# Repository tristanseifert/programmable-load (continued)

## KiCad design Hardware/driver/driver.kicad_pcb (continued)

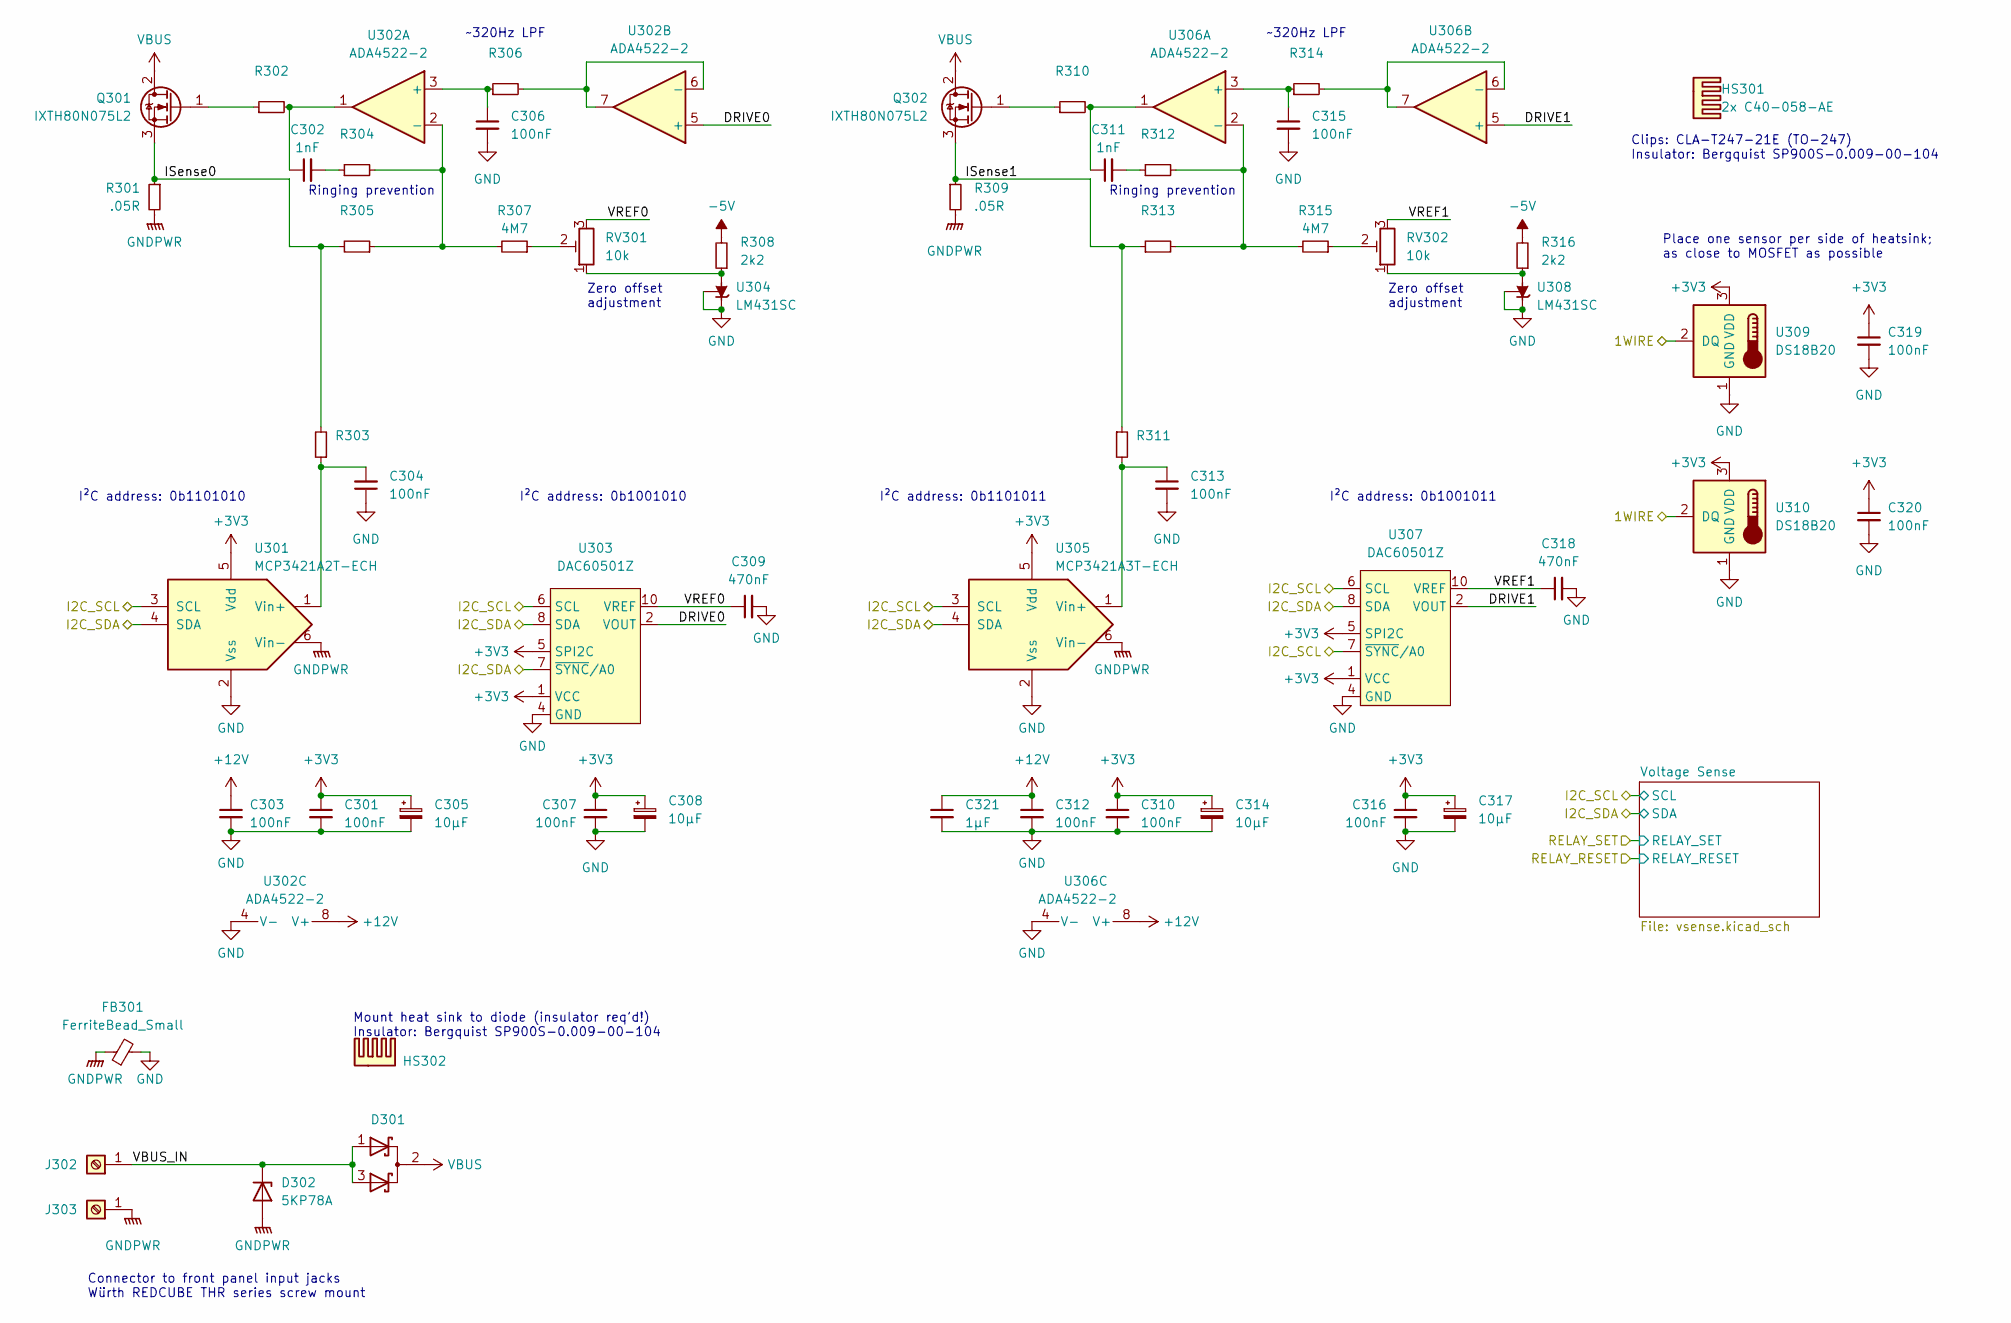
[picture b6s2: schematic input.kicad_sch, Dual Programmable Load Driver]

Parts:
C301, C303, C304, C306, C307, C310, C312, C313, C315, C316, C319, C320: 100nF; C_0805_2012Metric_Pad1.18x1.45mm_HandSolder
C302, C311: 1nF; C_0805_2012Metric_Pad1.18x1.45mm_HandSolder
C305, C308, C314, C317: 10µF; CP_EIA-3216-18_Kemet-A_Pad1.58x1.35mm_HandSolder; MPN TAJA106K016RNJ
C309, C318: 470nF; C_0805_2012Metric_Pad1.18x1.45mm_HandSolder; MPN CL21B474KAFNNNE
C321: 1µF; C_0805_2012Metric_Pad1.18x1.45mm_HandSolder; MPN CL21B105KBFNNNG
D301: DSA120C150QB; TO-247-3_Vertical; MPN DSA120C150QB
D302: 5KP78A; D_P600_R-6_P20.00mm_Horizontal; MPN 5KP78A
FB301: FerriteBead_Small; L_0805_2012Metric_Pad1.05x1.20mm_HandSolder; MPN MFBM1V2012-800-R
HS301: 2x C40-058-AE; C40-058-AE-DUAL; MPN C40-058-AE
HS302: WV-T247-101E; Ohmite-WA-T247-101E-MFG; MPN WV-T247-101E
J302, J303: Würth 74651194R; WE-74651194; MPN 74651194R
Q301, Q302: IXTH80N075L2; TO-247-3_Vertical
R301, R309: .05R; TO-247-2_Vertical
R302, R310: MPN WR08X101-JTL
R303, R306, R311, R314: MPN CR0805-FX-4991ELF
R304, R305, R312, R313: MPN CR0805-JW-102ELF
R307, R315: 4M7; R_0805_2012Metric_Pad1.20x1.40mm_HandSolder; MPN 260-4.7M-RC
R308, R316: 2k2; R_0805_2012Metric_Pad1.20x1.40mm_HandSolder; MPN RMC1/10-222JTP
RV301, RV302: 10k; Potentiometer_Nidec_Copal_CT94EY; MPN CT-94EY103
U301: MCP3421A2T-ECH; SOT-23-6_Handsoldering
U302, U306: ADA4522-2; SOIC-8_3.9x4.9mm_P1.27mm; MPN ADA4522-2ARZ
U303, U307: DAC60501Z; VSSOP-10_3x3mm_P0.5mm; MPN DAC60501ZDGSR
U304, U308: LM431SC; SOT-23; MPN LM431SCCMFX
U305: MCP3421A3T-ECH; SOT-23-6_Handsoldering
U309, U310: DS18B20; TO-92_Inline

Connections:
+3V3: C301.1, C305.1, C307.1, C308.1, C310.1, C314.1, C316.1, C317.1, C319.1, C320.1, U301.5 (Vdd), U303.1 (VCC), U303.5 (SPI2C), U305.5 (Vdd), U307.1 (VCC), U307.5 (SPI2C), U309.3 (VDD), U310.3 (VDD); also elsewhere on the board
+12V: C303.1, C312.1, C321.1, U302.8 (V+), U306.8 (V+); also elsewhere on the board
-5V: R308.2, R316.2; also elsewhere on the board
/1WIRE: U309.2 (DQ), U310.2 (DQ); also elsewhere on the board
/I2C_SCL: U301.3 (SCL), U303.6 (SCL), U305.3 (SCL), U307.6 (SCL), U307.7 (~SYNC/A0); also elsewhere on the board
/I2C_SDA: U301.4 (SDA), U303.7 (~SYNC/A0), U303.8 (SDA), U305.4 (SDA), U307.8 (SDA); also elsewhere on the board
/Input Stage/DRIVE0: U302.5 (+), U303.2 (VOUT)
/Input Stage/DRIVE1: U306.5 (+), U307.2 (VOUT)
/Input Stage/ISense0: Q301.3 (S), R301.1, R303.2, R305.2
/Input Stage/ISense1: Q302.3 (S), R309.1, R311.1, R313.1
/Input Stage/VBUS_IN: D301.1 (K), D301.3 (K), D302.1 (A1), J302.1
/Input Stage/VREF0: C309.1, RV301.3, U303.10 (VREF)
/Input Stage/VREF1: C318.1, RV302.3, U307.10 (VREF)
GND: C301.2, C303.2, C304.1, C305.2, C306.2, C307.2, C308.2, C309.2, C310.2, C312.2, C313.2, C314.2, C315.2, C316.2, C317.2, C318.2, C319.2, C320.2, C321.2, FB301.2, U301.2 (Vss), U302.4 (V-), U303.4 (GND), U304.1 (K), U304.2 (REF), U305.2 (Vss), U306.4 (V-), U307.4 (GND), U308.1 (K), U308.2 (REF), U309.1 (GND), U310.1 (GND); also elsewhere on the board
GNDPWR: D302.2 (A2), FB301.1, J303.1, R301.2, R309.2, U301.6 (Vin-), U305.6 (Vin-); also elsewhere on the board
unnamed: C302.1, R302.2, U302.1
unnamed: C302.2, R304.1
unnamed: C304.2, R303.1, U301.1 (Vin+)
unnamed: C306.1, R306.1, U302.3 (+)
unnamed: C311.1, R310.2, U306.1
unnamed: C311.2, R312.1
unnamed: C313.1, R311.2, U305.1 (Vin+)
unnamed: C315.1, R314.1, U306.3 (+)
unnamed: Q301.1 (G), R302.1
unnamed: Q302.1 (G), R310.1
unnamed: R304.2, R305.1, R307.2, U302.2 (-)
unnamed: R306.2, U302.6 (-), U302.7
unnamed: R307.1, RV301.2
unnamed: R308.1, RV301.1, U304.3 (A)
unnamed: R312.2, R313.2, R315.2, U306.2 (-)
unnamed: R314.2, U306.6 (-), U306.7
unnamed: R315.1, RV302.2
unnamed: R316.1, RV302.1, U308.3 (A)
VBUS: D301.2 (A), Q301.2 (D), Q302.2 (D); also elsewhere on the board

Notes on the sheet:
Zero offset adjustment
I²C address: 0b1101010
I²C address: 0b1001011
I²C address: 0b1001010
Clips: CLA-T247-21E (TO-247) Insulator: Bergquist SP900S-0.009-00-104
Ringing prevention
Place one sensor per side of heatsink; as close to MOSFET as possible
Connector to front panel input jacks Würth REDCUBE THR series screw mount
~320Hz LPF
I²C address: 0b1101011
Mount heat sink to diode (insulator req'd!) Insulator: Bergquist SP900S-0.009-00-104

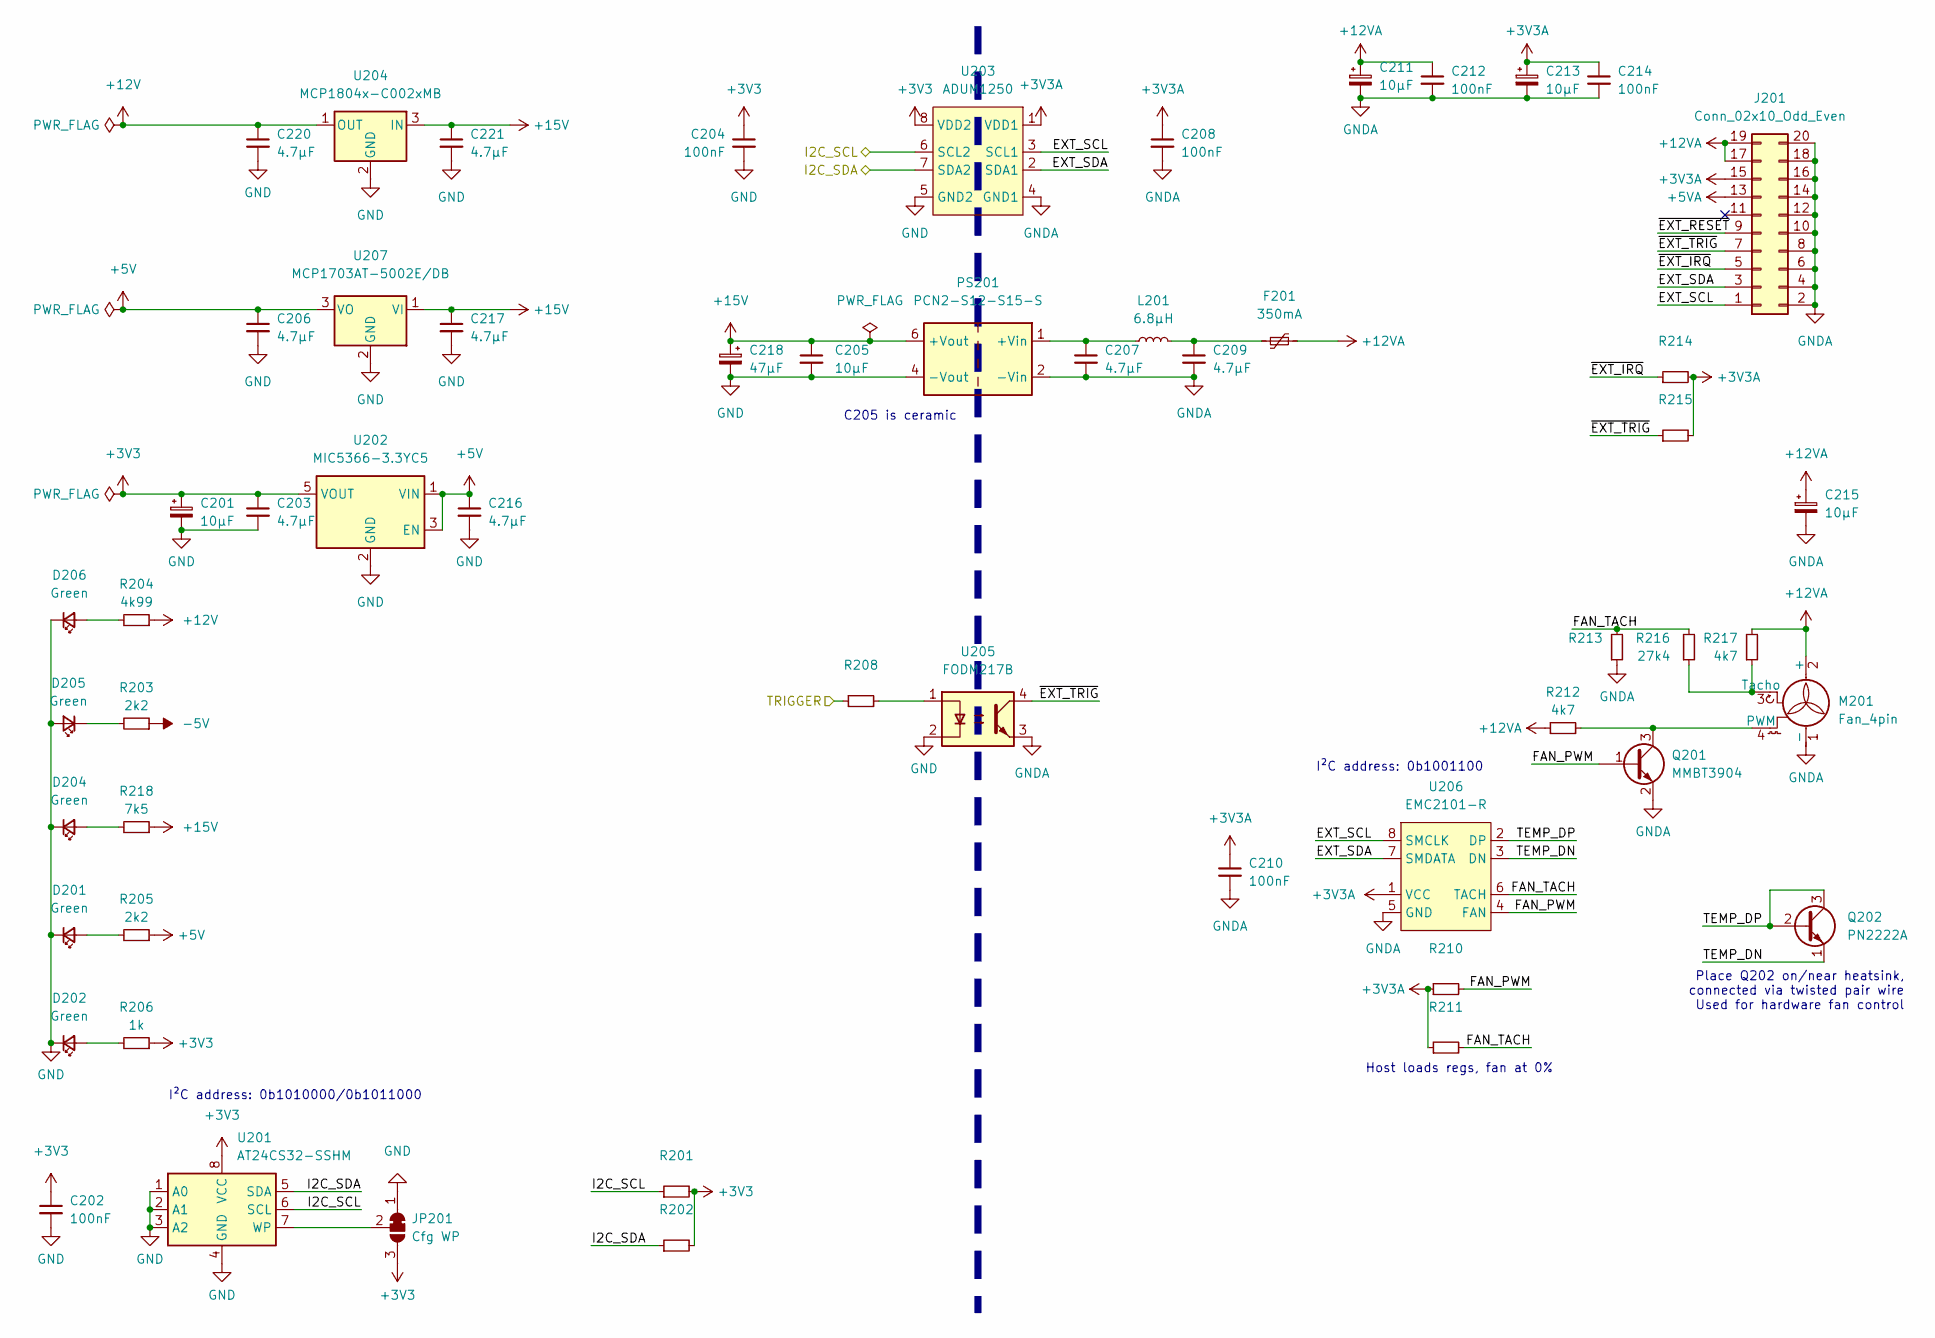
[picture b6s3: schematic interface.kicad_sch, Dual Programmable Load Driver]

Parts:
C201, C213: 10µF; CP_EIA-3216-18_Kemet-A_Pad1.58x1.35mm_HandSolder; MPN TAJA106K016RNJ
C202, C204, C208, C210, C212, C214: 100nF; C_0805_2012Metric_Pad1.18x1.45mm_HandSolder
C203, C206, C207, C209, C216, C217, C220, C221: 4.7µF; C_0805_2012Metric_Pad1.18x1.45mm_HandSolder; MPN CL21A475KAQNNNF
C205: 10µF; C_0805_2012Metric_Pad1.18x1.45mm_HandSolder; MPN TMK212BBJ106MG-T
C211: 10µF; CP_EIA-3528-21_Kemet-B_Pad1.50x2.35mm_HandSolder; MPN TAJB106K025TNJ
C215: 10µF; CP_Radial_D5.0mm_P2.00mm; MPN 860010472002
C218: 47µF; CP_Radial_D6.3mm_P2.50mm; MPN A750EK476M1EAAE040
D201, D202, D204, D205, D206: Green; LED_0805_2012Metric_Pad1.15x1.40mm_HandSolder; MPN 150080VS75000
F201: 350mA; Fuse_1210_3225Metric_Pad1.42x2.65mm_HandSolder; MPN 0ZCH0035FF2G
J201: Conn_02x10_Odd_Even; IDC-Header_2x10_P2.54mm_Vertical; MPN T821120A1S100CEU
JP201: Cfg WP; PinHeader_1x03_P2.54mm_Vertical
L201: 6.8µH; L_Taiyo-Yuden_NR-24xx_HandSoldering; MPN NRH2410T6R8MN
M201: Fan_4pin; Molex-47053-1000-MFG; MPN 47053-1000
PS201: PCN2-S12-S15-S; CONV_PCN2-S12-S15-S
Q201: MMBT3904; SOT-323_SC-70_Handsoldering; MPN MMBT3904,215
Q202: PN2222A; TO-92_Inline; MPN PN2222ATA
R201, R202, R214, R215: MPN RMC1/10-222JTP
R203, R205: 2k2; R_0805_2012Metric_Pad1.20x1.40mm_HandSolder; MPN RMC1/10-222JTP
R204: 4k99; R_0805_2012Metric_Pad1.20x1.40mm_HandSolder; MPN CR0805-FX-4991ELF
R206: 1k; R_0805_2012Metric_Pad1.20x1.40mm_HandSolder; MPN CR0805-JW-102ELF
R208: MPN CR0805-JW-102ELF
R210, R211, R213: MPN RMC1/10-103JTP
R212, R217: 4k7; R_0805_2012Metric_Pad1.20x1.40mm_HandSolder
R216: 27k4; R_0805_2012Metric_Pad1.20x1.40mm_HandSolder
R218: 7k5; R_0805_2012Metric_Pad1.20x1.40mm_HandSolder; MPN WR08X752 JTL
U201: AT24CS32-SSHM; SOIC-8_3.9x4.9mm_P1.27mm
U202: MIC5366-3.3YC5; SOT-353_SC-70-5; MPN MIC5366-3.3YC5-TR
U203: ADUM1250; SOIC-8_3.9x4.9mm_P1.27mm
U204: MCP1804x-C002xMB; SOT-89-3; MPN MCP1804T-C002I/MB
U205: FODM217B; SOP-4_4.4x2.6mm_P1.27mm; MPN FODM217B
U206: EMC2101-R; MSOP-8_3x3mm_P0.65mm; MPN EMC2101-R-ACZL-TR
U207: MCP1703AT-5002E/DB; SOT-223-3_TabPin2; MPN MCP1703AT-5002E/DB

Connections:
+3V3: C201.1, C202.1, C203.1, C204.1, JP201.3 (B), R201.2, R202.2, R206.1, U201.8 (VCC), U202.5 (VOUT), U203.8 (VDD2); also elsewhere on the board
+3V3A: C208.1, C210.1, C213.1, C214.1, J201.15, R210.1, R211.1, R214.2, R215.2, U203.1 (VDD1), U206.1 (VCC)
+5V: C206.1, C216.1, R205.1, U202.1 (VIN), U202.3 (EN), U207.3 (VO); also elsewhere on the board
+5VA: J201.13
+12V: C220.1, R204.1, U204.1 (OUT); also elsewhere on the board
+12VA: C211.1, C212.1, C215.1, F201.2, J201.17, J201.19, M201.2 (+), R212.2, R217.2; also elsewhere on the board
+15V: C205.1, C217.1, C218.1, C221.1, PS201.6 (+Vout), R218.1, U204.3 (IN), U207.1 (VI); also elsewhere on the board
-5V: R203.1; also elsewhere on the board
/External Interface/EXT_SCL: J201.1, U203.3 (SCL1), U206.8 (SMCLK)
/External Interface/EXT_SDA: J201.3, U203.2 (SDA1), U206.7 (SMDATA)
/External Interface/FAN_PWM: Q201.1 (B), R210.2, U206.4 (FAN)
/External Interface/FAN_TACH: R211.2, R213.2, R216.2, U206.6 (TACH)
/External Interface/TEMP_DN: Q202.1 (E), U206.3 (DN)
/External Interface/TEMP_DP: Q202.2 (B), Q202.3 (C), U206.2 (DP)
/External Interface/~EXT_IRQ: J201.5, R214.1
/External Interface/~EXT_RESET: J201.9
/External Interface/~EXT_TRIG: J201.7, R215.1, U205.4
/I2C_SCL: R201.1, U201.6 (SCL), U203.6 (SCL2); also elsewhere on the board
/I2C_SDA: R202.1, U201.5 (SDA), U203.7 (SDA2); also elsewhere on the board
/TRIGGER: R208.2; also elsewhere on the board
GND: C201.2, C202.2, C203.2, C204.2, C205.2, C206.2, C216.2, C217.2, C218.2, C220.2, C221.2, D201.1 (K), D202.1 (K), D204.1 (K), D205.2 (A), D206.1 (K), JP201.1 (A), PS201.4 (-Vout), U201.1 (A0), U201.2 (A1), U201.3 (A2), U201.4 (GND), U202.2 (GND), U203.5 (GND2), U204.2 (GND), U205.2, U207.2 (GND); also elsewhere on the board
GNDA: C207.2, C208.2, C209.2, C210.2, C211.2, C212.2, C213.2, C214.2, C215.2, J201.2, J201.4, J201.6, J201.8, J201.10, J201.12, J201.14, J201.16, J201.18, J201.20, M201.1 (-), PS201.2 (-Vin), Q201.2 (E), R213.1, U203.4 (GND1), U205.3, U206.5 (GND); also elsewhere on the board
unnamed: C207.1, L201.1, PS201.1 (+Vin)
unnamed: C209.1, F201.1, L201.2
unnamed: D201.2 (A), R205.2
unnamed: D202.2 (A), R206.2
unnamed: D204.2 (A), R218.2
unnamed: D205.1 (K), R203.2
unnamed: D206.2 (A), R204.2
unnamed: JP201.2 (C), U201.7 (WP)
unnamed: M201.3 (Tacho), R216.1, R217.1
unnamed: M201.4 (PWM), Q201.3 (C), R212.1
unnamed: R208.1, U205.1

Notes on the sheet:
I²C address: 0b1010000/0b1011000
C205 is ceramic
Host loads regs, fan at 0%
Place Q202 on/near heatsink, connected via twisted pair wire Used for hardware fan control
I²C address: 0b1001100

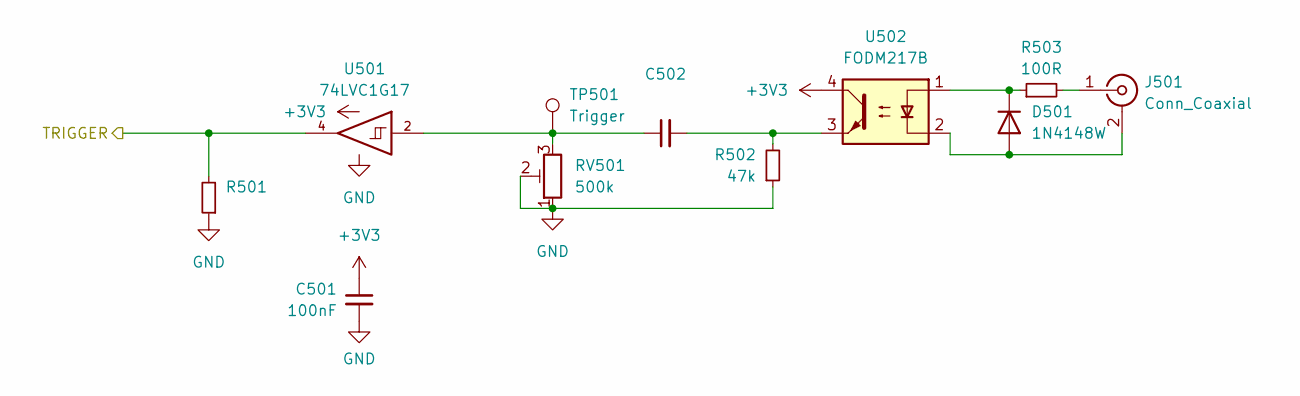
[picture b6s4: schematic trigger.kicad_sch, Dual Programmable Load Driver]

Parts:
C501: 100nF; C_0805_2012Metric_Pad1.18x1.45mm_HandSolder
C502: MPN CL21B105KBFNNNG
D501: 1N4148W; D_SOD-123; MPN 1N4148W-AU_R1_000A1
J501: Conn_Coaxial; CONN_1-1337543-0; MPN 1-1634624-0
R501: MPN RMC1/10-103JTP
R502: 47k; R_0805_2012Metric_Pad1.20x1.40mm_HandSolder; MPN RMC1/10-473JTP
R503: 100R; R_0805_2012Metric_Pad1.20x1.40mm_HandSolder; MPN WR08X101-JTL
RV501: 500k; Potentiometer_Nidec_Copal_CT94EW; MPN CT-94EW504
TP501: Trigger; TestPoint_Keystone_5000-5004_Miniature; MPN 5004
U501: 74LVC1G17; SOT-23-5_HandSoldering; MPN SN74LVC1G17DBVRG4
U502: FODM217B; SOP-4_4.4x2.6mm_P1.27mm; MPN FODM217B

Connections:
+3V3: C501.1, U501.5 (VCC), U502.4; also elsewhere on the board
/TRIGGER: R501.2, U501.4; also elsewhere on the board
GND: C501.2, R501.1, R502.1, RV501.1, RV501.2, U501.3 (GND); also elsewhere on the board
unnamed: C502.1, RV501.3, TP501.1, U501.2
unnamed: C502.2, R502.2, U502.3
unnamed: D501.1 (K), R503.1, U502.1
unnamed: D501.2 (A), J501.2 (Ext), U502.2
unnamed: J501.1 (In), R503.2

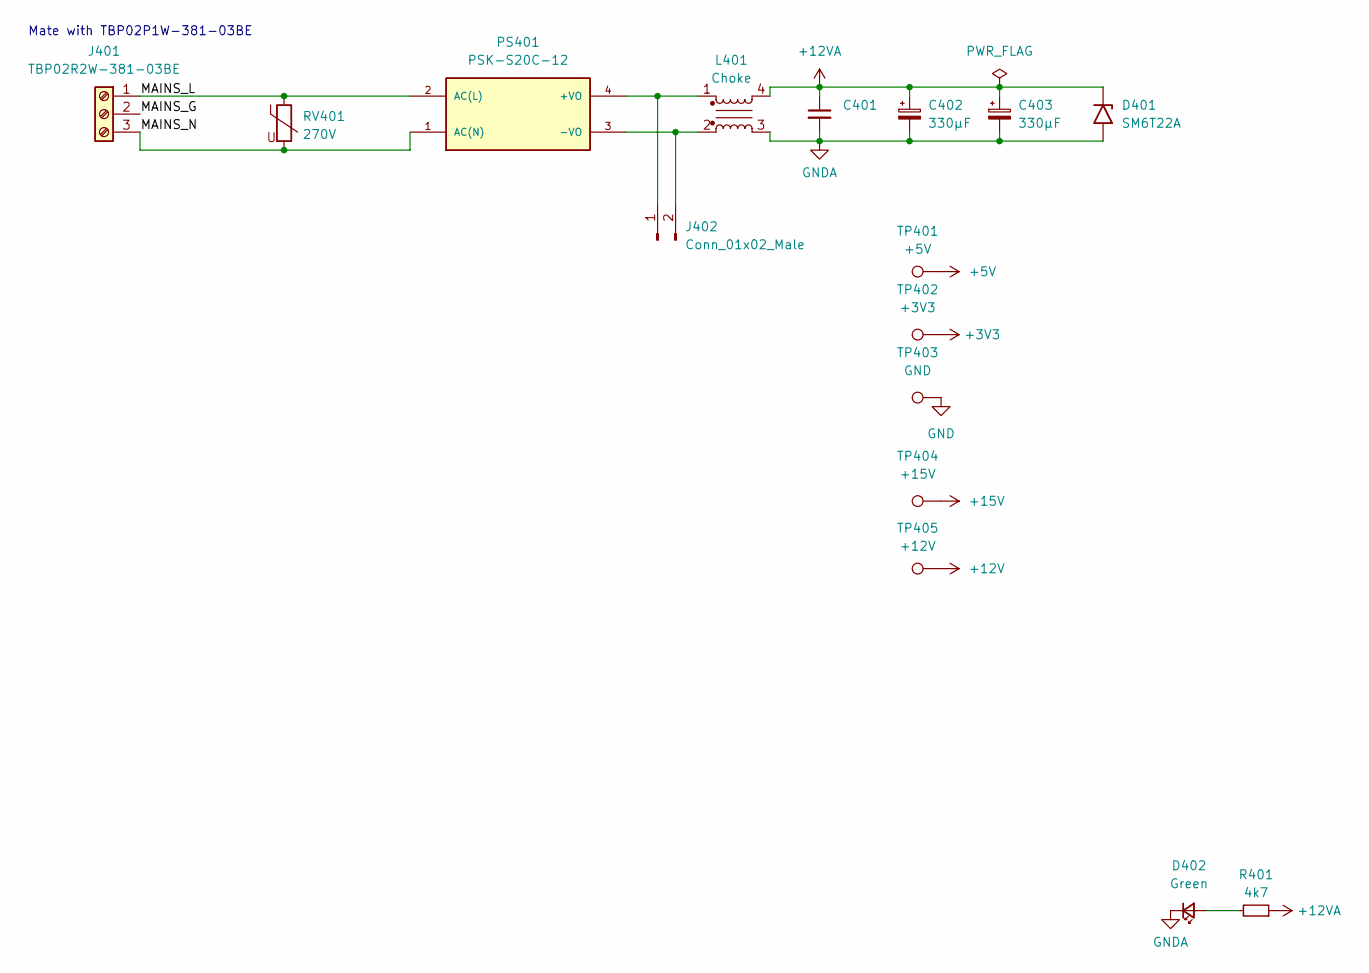
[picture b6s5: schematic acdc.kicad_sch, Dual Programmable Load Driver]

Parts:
C401: MPN CL21B105KBFNNNG
C402, C403: 330µF; CP_Radial_D8.0mm_P3.50mm; MPN A750KS337M1EAAE018
D401: SM6T22A; D_SMB
D402: Green; LED_0805_2012Metric_Pad1.15x1.40mm_HandSolder; MPN 150080VS75000
J401: TBP02R2W-381-03BE; CUI_TBP02R2W-381-03BE
J402: Conn_01x02_Male; JST_VH_B2P-VH-B_1x02_P3.96mm_Vertical
L401: Choke; TDK-ACM1513-0-0-MFG; MPN ACM1513-551-2PL-TLHF
PS401: PSK-S20C-12; CONV_PSK-S20C-12; PARTREV 1.0
R401: 4k7; R_0805_2012Metric_Pad1.20x1.40mm_HandSolder
RV401: 270V; RV_Disc_D7mm_W4.2mm_P5mm; MPN 271KD07-TR
TP401: +5V; TestPoint_Keystone_5000-5004_Miniature; MPN 5000
TP402: +3V3; TestPoint_Keystone_5000-5004_Miniature; MPN 5000
TP403: GND; TestPoint_Keystone_5000-5004_Miniature; MPN 5001
TP404: +15V; TestPoint_Keystone_5000-5004_Miniature; MPN 5000
TP405: +12V; TestPoint_Keystone_5000-5004_Miniature; MPN 5000

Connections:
+3V3: TP402.1; also elsewhere on the board
+5V: TP401.1; also elsewhere on the board
+12V: TP405.1; also elsewhere on the board
+12VA: C401.1, C402.1, C403.1, D401.1 (A1), L401.4, R401.1; also elsewhere on the board
+15V: TP404.1; also elsewhere on the board
/Mains Supply (Optional)/MAINS_G: J401.2
/Mains Supply (Optional)/MAINS_L: J401.1, PS401.2 (AC(L)), RV401.1
/Mains Supply (Optional)/MAINS_N: J401.3, PS401.1 (AC(N)), RV401.2
GND: TP403.1; also elsewhere on the board
GNDA: C401.2, C402.2, C403.2, D401.2 (A2), D402.1 (K), L401.3; also elsewhere on the board
unnamed: D402.2 (A), R401.2
unnamed: J402.1, L401.1, PS401.4 (+VO)
unnamed: J402.2, L401.2, PS401.3 (-VO)

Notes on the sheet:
Mate with TBP02P1W-381-03BE

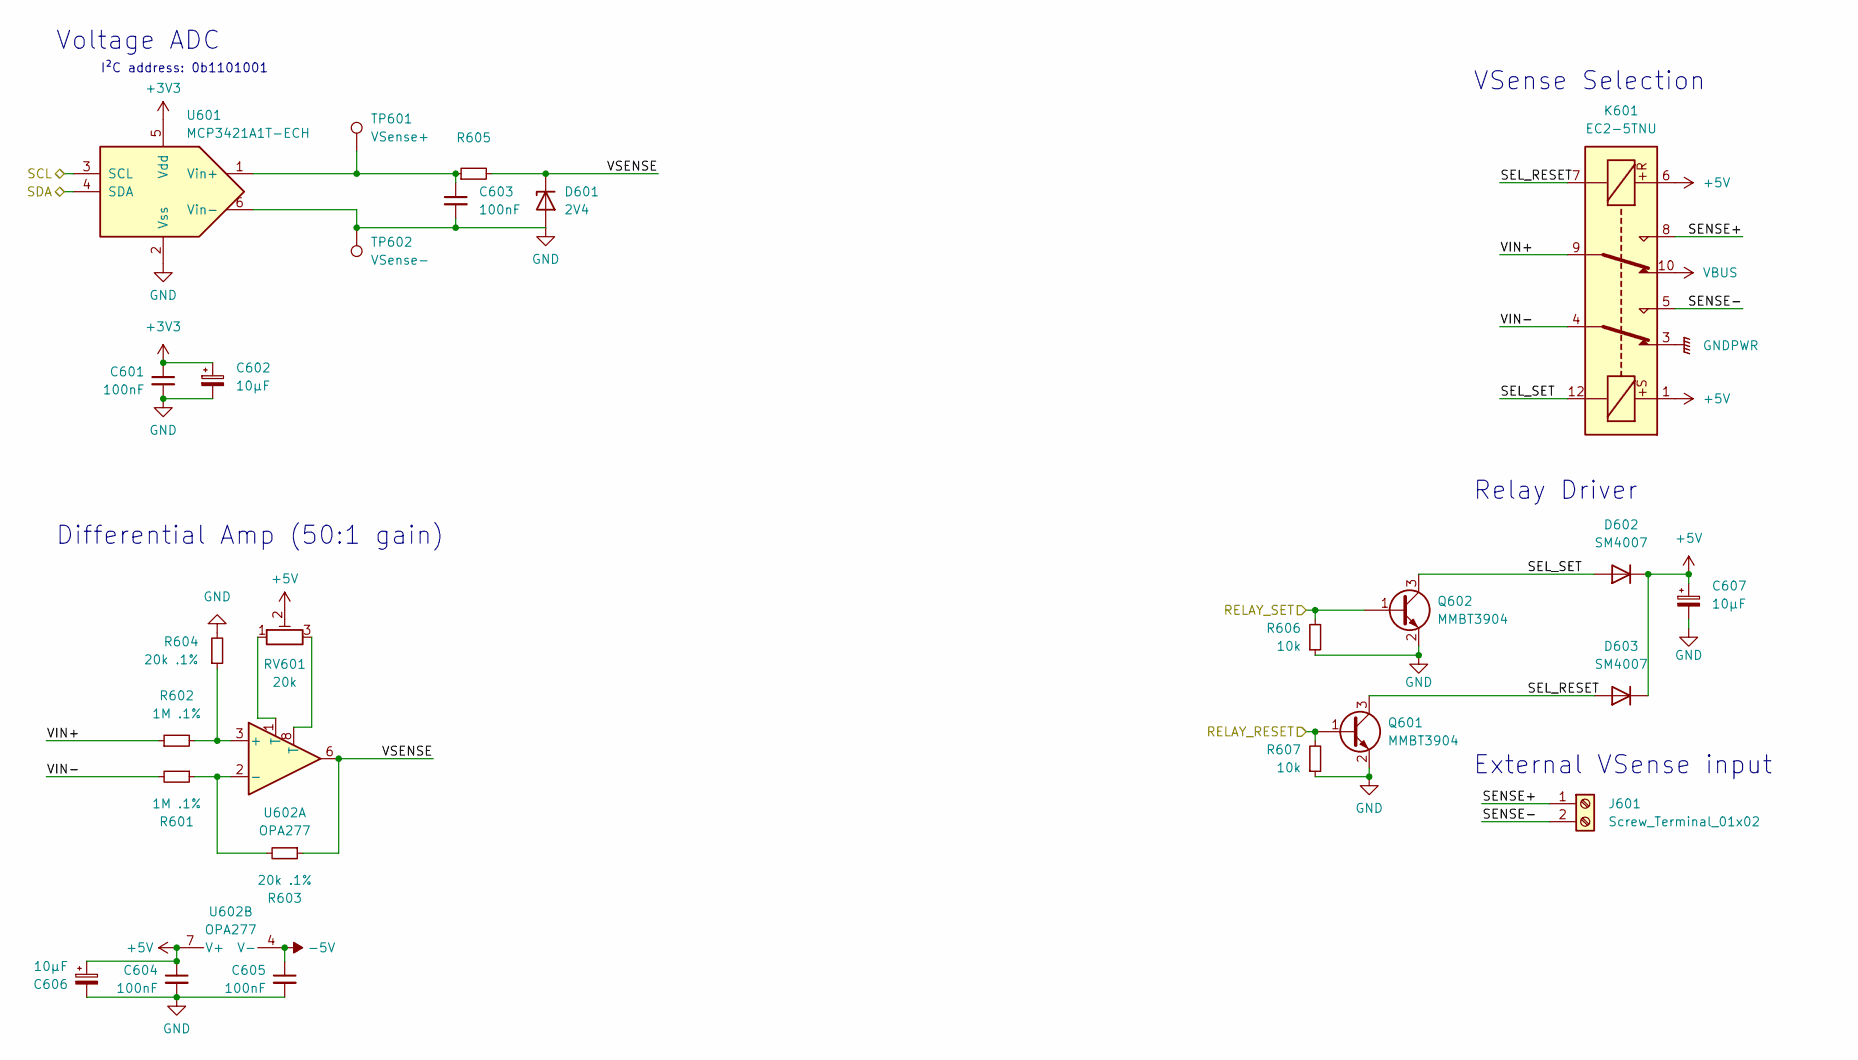
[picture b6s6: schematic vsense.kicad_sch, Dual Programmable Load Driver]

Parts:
C601, C603, C604, C605: 100nF; C_0805_2012Metric_Pad1.18x1.45mm_HandSolder
C602, C606: 10µF; CP_EIA-3216-18_Kemet-A_Pad1.58x1.35mm_HandSolder; MPN TAJA106K016RNJ
C607: 10µF; CP_Radial_D5.0mm_P2.00mm; MPN 860010472002
D601: 2V4; D_MiniMELF_Handsoldering; MPN BZV55-C2V4,135
D602, D603: SM4007; D_SMA_Handsoldering; MPN FM4007W-W
J601: Screw_Terminal_01x02; CUI_TBL002A-350-02GR-2OR; MPN TBL002A-350-02GR-2OR
K601: EC2-5TNU; Relay_DPDT_Kemet_EC2_DoubleCoil; MPN EC2-5TNU
Q601, Q602: MMBT3904; SOT-323_SC-70_Handsoldering; MPN MMBT3904,215
R601, R602: 1M .1%; R_0805_2012Metric_Pad1.20x1.40mm_HandSolder; MPN RN73C2A1M0BTDF
R603, R604: 20k .1%; R_0805_2012Metric_Pad1.20x1.40mm_HandSolder; MPN ERA-6ARB203V
R605: MPN CR0805-FX-4991ELF
R606, R607: 10k; R_0805_2012Metric_Pad1.20x1.40mm_HandSolder; MPN RMC1/10-103JTP
RV601: 20k; Potentiometer_Nidec_Copal_CT94EY; MPN CT-94EY203
TP601: VSense+; TestPoint_Keystone_5000-5004_Miniature; MPN 5004
TP602: VSense-; TestPoint_Keystone_5000-5004_Miniature; MPN 5001
U601: MCP3421A1T-ECH; SOT-23-6_Handsoldering
U602: OPA277; SOIC-8_3.9x4.9mm_P1.27mm

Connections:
+3V3: C601.1, C602.1, U601.5 (Vdd); also elsewhere on the board
+5V: C604.1, C606.1, C607.1, D602.1 (K), D603.1 (K), K601.1, K601.6, RV601.2, U602.7 (V+); also elsewhere on the board
-5V: C605.1, U602.4 (V-); also elsewhere on the board
/I2C_SCL: U601.3 (SCL); also elsewhere on the board
/I2C_SDA: U601.4 (SDA); also elsewhere on the board
/Input Stage/Voltage Sense/SEL_RESET: D603.2 (A), K601.7, Q601.3 (C)
/Input Stage/Voltage Sense/SEL_SET: D602.2 (A), K601.12, Q602.3 (C)
/Input Stage/Voltage Sense/SENSE+: J601.1, K601.8
/Input Stage/Voltage Sense/SENSE-: J601.2, K601.5
/Input Stage/Voltage Sense/VIN+: K601.9, R602.1
/Input Stage/Voltage Sense/VIN-: K601.4, R601.2
/Input Stage/Voltage Sense/VSENSE: D601.1 (K), R603.1, R605.2, U602.6
/SENSE_RST: Q601.1 (B), R607.2; also elsewhere on the board
/SENSE_SET: Q602.1 (B), R606.2; also elsewhere on the board
GND: C601.2, C602.2, C603.2, C604.2, C605.2, C606.2, C607.2, D601.2 (A), Q601.2 (E), Q602.2 (E), R604.2, R606.1, R607.1, TP602.1, U601.2 (Vss), U601.6 (Vin-); also elsewhere on the board
GNDPWR: K601.3; also elsewhere on the board
unnamed: C603.1, R605.1, TP601.1, U601.1 (Vin+)
unnamed: R601.1, R603.2, U602.2 (-)
unnamed: R602.2, R604.1, U602.3 (+)
unnamed: RV601.1, U602.1 (T)
unnamed: RV601.3, U602.8 (T)
VBUS: K601.10; also elsewhere on the board

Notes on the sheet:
External VSense input
Voltage ADC
Differential Amp (50:1 gain)
I²C address: 0b1101001
Relay Driver
VSense Selection

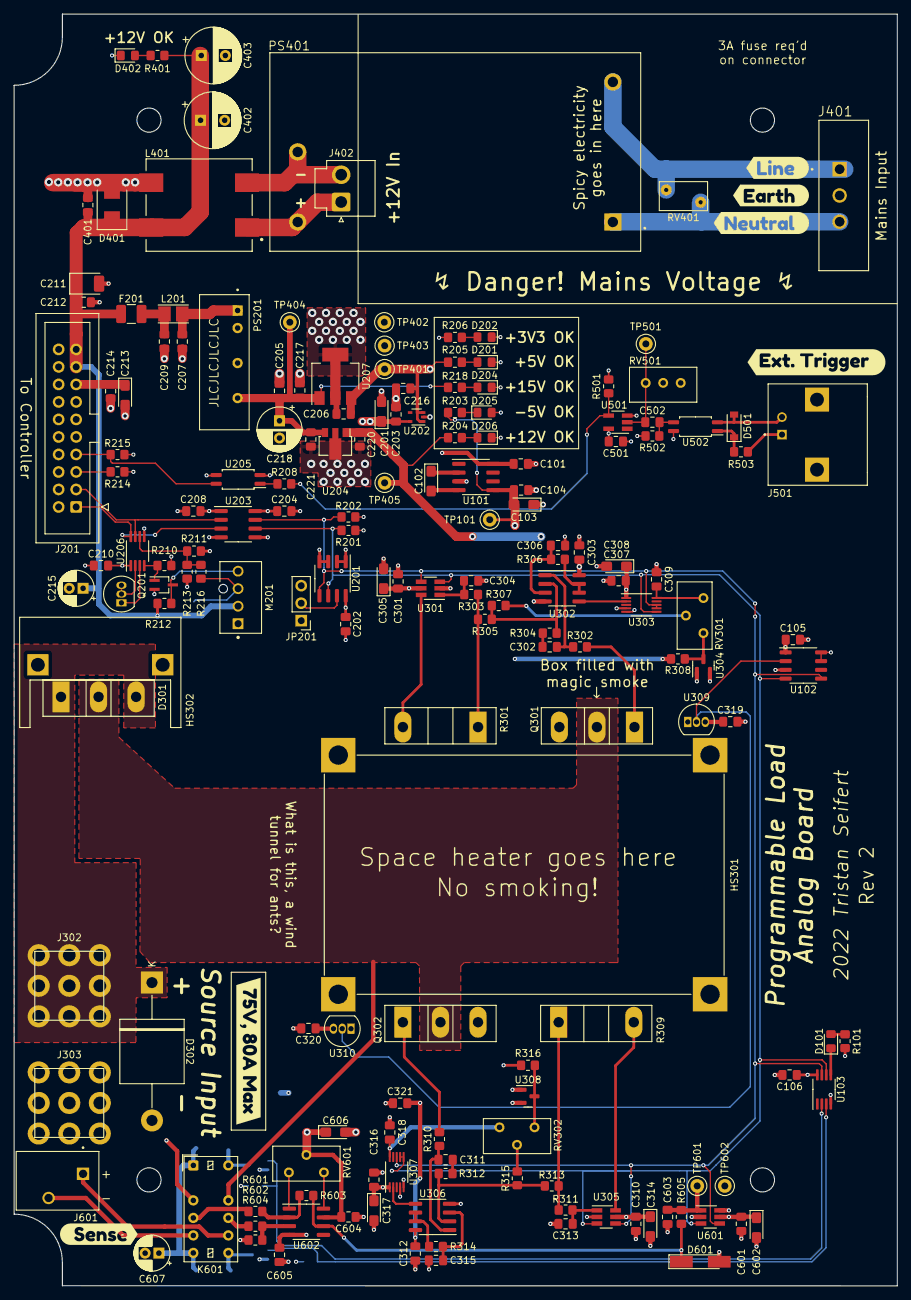
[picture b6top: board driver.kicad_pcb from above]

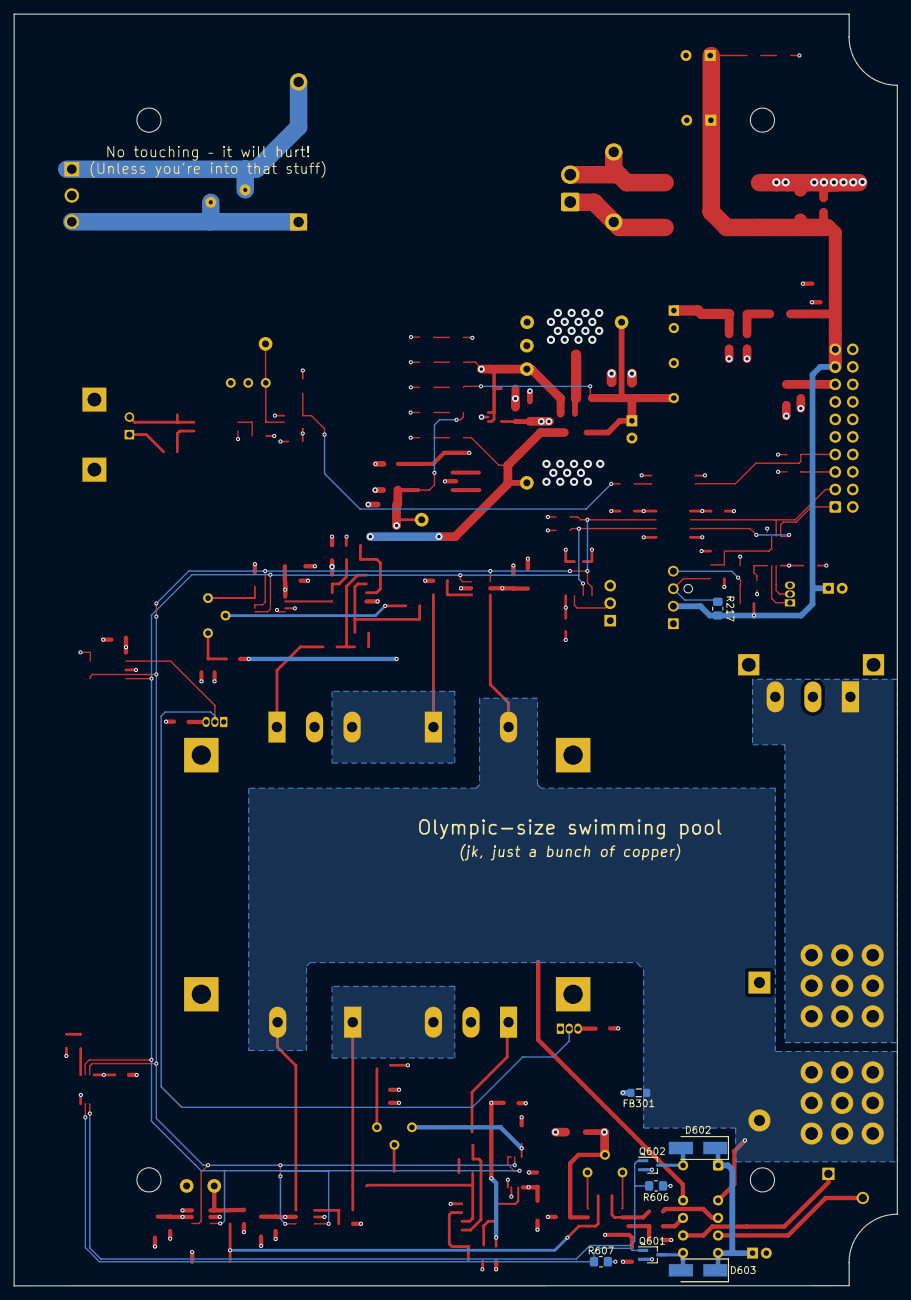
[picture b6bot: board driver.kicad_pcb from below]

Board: 4 copper layers, 128.1 x 184.5 mm, 189 parts (8 on the bottom side), 87 nets.

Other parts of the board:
kibuzzard-6248DD82: G***; kibuzzard-6248DD82
kibuzzard-6248DDB7: G***; kibuzzard-6248DDB7
kibuzzard-6248DE02: G***; kibuzzard-6248DE02
kibuzzard-6248DE32: G***; kibuzzard-6248DE32
kibuzzard-6248DECB: G***; kibuzzard-6248DECB
kibuzzard-6250772E: G***; kibuzzard-6250772E

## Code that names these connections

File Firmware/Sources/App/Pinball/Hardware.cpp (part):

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 *
 * Initialize SERCOM4 with DOPO=2, DIPO=0 so that the following pins are used:
 * -  /CS: PB14/PAD2
 * -  SCK: PB13/PAD1
 * - MOSI: PB15/PAD3
 * - MISO: PB12/PAD0
 *
 * Additionally, the display command/data output is configured (PA04)
 */
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 *
 * This configures various IOs for the user interface:
 *
 * - /FRONT_RESET: PA5 (external pull-up)
 */
void Hw::InitMisc() {
    // front panel reset line
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 *
 * The following IOs are configured:
 *
 * - STATUS_R: PB05
 * - STATUS_G: PB04
 * - STATUS_B: PA03
 *
 * Pulling them low will illuminate the LED.
 */
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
